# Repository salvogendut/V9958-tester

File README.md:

# V9938 / V9958 Pico Functional Tester

This is an all-through-hole carrier board that performs a behavioral test of a socketed Yamaha V9938 or V9958 video display processor. An original RP2040 Raspberry Pi Pico controls the VDP, tests its dedicated 128 KiB VRAM, measures its clocks and analog RGB outputs, and reports the result on green/red LEDs, USB serial, and an on-screen message through an Omega-compatible DIN RGB output.

The current full-size board is **revision 0.5**. U10 is a through-hole TI LM393P dual comparator and U11 is an SN74HC14N sync buffer. The board passes KiCad ERC, DRC and schematic/PCB parity checks. Qualification on real VDPs is pending. [0.5 Gerbers](fabrication/V9958-Tester-rev0.5-gerbers.zip) · [0.5 BOM](docs/BOM.csv)

For a board already marked **0.4**, fit the MAX942CPA+ specified for that circuit. The LM393P requires the revised input dividers and output circuitry. [0.4 BOM](https://github.com/salvogendut/V9958-tester/blob/81ad3057a48962fd7bea91b546fce25a6f905914/docs/BOM.csv) · [Original 0.3 BOM](docs/V9958-Tester-rev0.3-BOM.csv)

**Disconnect USB and set SW2 to the model printed on the chip before inserting it in U3.** The V9938 uses pin 21 as a video output. Selecting V9958 connects that pin directly to the filtered 5 V rail and can damage a V9938. The original 0.3, B0 and B2 tester PCBs have this direct connection permanently. Use a board marked **0.4 or 0.5**, **B1 or B1.1**, or **B2.1 or B2.2 SRAM** for V9938 testing.

**Polarity correction for full-size v0.3 and early v0.4 boards.** Four electrolytics (C25, C26, C27 and C28) have an extra printed `+` on the negative side. On all seven radial capacitors, fit the positive lead to the rounded-square pad 1 and the striped negative lead to circular pad 2. With the components facing you and the DIN socket at the upper right, the stripe goes on the **right**. The corrected [v0.4 Gerbers](fabrication/V9958-Tester-rev0.4-silk2-gerbers.zip) have a single `+` beside each positive capacitor pad. [Assembly checks](docs/TEST-PROCEDURE.md)

## Board renderings

Select a view to open the full-resolution KiCad rendering.

| PCB revision | Assembled | Bare component side | Bare solder side |
|---|---|---|---|
| **Full-size tester 0.5** · [Assembled top view](docs/V9958-Tester-top.png) |  |  |  |
| **Compact DRAM tester B1.1** · [Assembled top view](revision-b/docs/V9958-Tester-RevB-top.png) |  |  |  |
| **Compact SRAM tester B2.2** · [Assembled top view](revision-b2-sram/docs/V9958-Tester-RevB2-SRAM-top.png) |  |  |  |

On the full-size 0.5, the RGB cable plugs into J1 from outside the top edge. The four VRAM sockets sit above U3, and the Pico USB connector faces right. SW2 sits above the TEST button. Disconnect USB before selecting the VDP model. All four boards print component references and BOM values on the component side, including the 1% resistor tolerances.

[Earlier renderings for 0.4, B1 and B2.1](https://github.com/salvogendut/V9958-tester/blob/81ad3057a48962fd7bea91b546fce25a6f905914/README.md#board-renderings)

## Revision B family and video daughterboard

Revision B separates the functional tester from the optional monitor output. The
[Revision B core](revision-b/) keeps the socketed VDP, four 41464 VRAMs, one
SN74LVC245 data transceiver, one SN74LVC244 monitor buffer, the oscillator,
power integrity, RGB loads and Pico. The Pico drives the VDP control inputs
directly through 330-ohm series resistors. The CXA1645 and DIN connector have
moved to a separate [RGB DIN daughterboard](video-daughterboard/).

The experimental [Revision B2 SRAM board](revision-b2-sram/) replaces the four
41464 DRAMs with one AS6C1008-55PCN 128Kx8 SRAM, an SN74AHCT573 row-address
latch and an SN74AHCT08 CAS-to-output-enable gate. The Pico still controls and
tests the selected VDP; it does not emulate the timing-critical video RAM bus.

B2 is smaller at 160 x 110 mm and remains entirely through-hole. It includes
dedicated `/RAS`, `/CAS0`, `/CAS1`, SRAM `/OE` and SRAM `/WE` test points. Its
static KiCad checks pass, but its narrow SRAM timing margin has not been
qualified on hardware. Do not use an unqualified B2 fixture to reject a VDP;
confirm failures on a qualified DRAM fixture or a working Omega configured for that chip.

The two boards use a keyed, straight-through 2x3 IDC cable: pin 1 GND, pin 2
+5 V, pin 3 red, pin 4 green, pin 5 blue and pin 6 composite sync. Revision B
passes or fails without the daughterboard; connect it only when an Omega-style
15.6 kHz RGB monitor output and on-screen result are wanted. Both designs are
unbuilt prototypes and have their own BOM, schematic PDF, validation record,
assembly drawing and Gerber archive.

## What it tests

- CPU bus operation through 3.3 V/5 V level translation.
- VDP identification through status register 1, bits 5–1. ID 0 selects V9938 tests and ID 2 selects V9958 tests. Other IDs fail identification.
- Two full address-dependent passes over 128 KiB of local VRAM.
- Approximately 3.58 MHz CPUCLK and 15.6 kHz HSYNC/CSYNC.
- Vertical-blank interrupt assertion and status acknowledgement.
- Red, green, and blue analog-channel response through loaded, divided ADC inputs.

A green LED means all behavioral checks passed. A red LED means at least one check failed; USB serial gives the stage and measurements. A pass is **not forensic proof** that the package was manufactured by Yamaha. A sufficiently compatible clone could pass.

The firmware also leaves a 40-column PAL result screen visible on the DIN RGB output. It shows `PASS` or `FAIL`, the numeric stage code, and the failed subsystem. The screen and USB result identify the detected model. Compare it with the package marking.

## Construction

The tester PCB itself uses no SMD parts. Fit the Pico on two 1x20 through-hole socket strips; the Pico module is, of course, an already assembled module containing SMD components. Use sockets for U1–U9, including a suitable SDIP-64 socket at U3. On revision 0.5, fit the LM393P at U10, the SN74HC14N at U11, and the C&K JS202011CQN model selector at SW2.

Important parts:

- U3 footprint: custom SDIP-64, 1.778 mm pin pitch, 19.05 mm row spacing.
- U5–U8: four 41464-compatible 64Kx4 DRAMs, 120 ns or faster.
- U1: SN74LVC245AN, powered from 3.3 V.
- U2: SN74AHCT244N, powered from 5 V.
- U4: SN74LVC244AN, powered from 3.3 V.
- U9: CXA1645P in DIP-24, used as the three-channel 75-ohm RGB cable buffer.
- J1 takes a Same Sky **SDS-80J**, a standard full-size 270° right-angle DIN-8 socket. It accepts an Omega-wired RGB cable. The shielded SDF-80J with a date code after 03/03/2022 also fits the PCB drawing. [SDS-80J drawing, p. 5](https://www.sameskydevices.com/product/resource/sds-j.pdf) · [DigiKey Italy](https://www.digikey.it/it/products/detail/same-sky-formerly-cui-devices/SDS-80J/97041)
- Y1: 21.477270 MHz crystal; C1 is the 30 pF oscillator trimmer.
- F1: Bourns MF-RHT100 resettable fuse, 1.0 A hold / 1.8 A trip.

The grouped [BOM](docs/BOM.csv), [schematic PDF](docs/V9958-Tester-Schematic.pdf), and [test procedure](docs/TEST-PROCEDURE.md) are in `docs/`. The [fabrication directory](fabrication/) contains the Gerbers and drill files for each full-size dual-model revision.

## Power and handling

Power the board only through the Pico USB connector, from a good 5 V supply capable of at least 1 A. For first power-up, use a current-limited bench supply or USB power limiter. Never insert or remove the V9958, VRAM, logic chips, or Pico while powered.

The board provides native 15.6 kHz PAL RGB through J1. It is suitable for an Omega/MSX RGB cable and a compatible RGB monitor or SCART input; it is **not 31 kHz VGA** and must not be connected to a VGA-only display. J1 follows the Omega assignments: pin 1 ground, pin 3 AV control, pin 4 attenuated composite sync, pin 5 RGB/YS control, pin 6 red, pin 7 green, and pin 8 blue. Pin 2 (audio on an Omega) is unconnected because the tester has no audio source.

U9 reproduces the Omega-style buffered RGB path: 0.1 uF input coupling, CXA1645 clamping/drivers, and 75 ohm plus 220 uF output coupling per colour. J1 pin 4 carries sync only, not composite video. Scope points remain available for 5 V, 3.3 V, ground, CPUCLK, HSYNC, CSYNC, and raw R/G/B.

## Firmware

Firmware source is in `firmware/`. With a Pico SDK toolchain installed:

```sh
export PICO_SDK_PATH=/path/to/pico-sdk
cmake -S firmware -B firmware/build -DPICO_BOARD=pico
cmake --build firmware/build -j4
```

Copy the supplied [full-size tester UF2](firmware/v9958_tester.uf2) or your local build to a Pico in BOOTSEL mode. The program runs once at power-up and again whenever SW1 is pressed. USB CDC serial prints the clock counts, VDP ID, first VRAM mismatch if any, interrupt result, RGB ADC readings, and final stage code. At completion it programs the VDP for PAL text mode and shows the same result through J1.

The compact boards use the shared source. Their images are [B1/B1.1 DRAM](revision-b/firmware/v9958_tester_revb.uf2) and [B2.1/B2.2 SRAM](revision-b2-sram/firmware/v9958_tester_revb2.uf2). They have no TEST
button; send `R` over USB serial to repeat the test.

## Design files and regeneration

- `V9958-Tester.kicad_sch`: native KiCad 10 schematic.
- `V9958-Tester.kicad_pcb`: two-layer routed board with GND pours.
- `V9958-Tester.kicad_pro`: project settings.
- `V9958-Tester.pretty/` contains the VDP socket, trimmer, and Same Sky DIN-8 footprints.
- `tools/`: deterministic schematic, footprint, placement, finish, and BOM generators.

The routing was completed with Freerouting and then imported and checked by KiCad. The checked-in PCB is the release artifact; rerunning the placement generator intentionally produces an unrouted board.

## Known prototype limitations

- RGB pass thresholds are conservative defaults and must be calibrated on known-good samples of both models.
- The full VRAM test and VDP port timing must be verified on physical hardware.
- Socket/ZIF mechanical fit must be checked against the exact part you intend to buy.
- CXA1645 RGB amplitude, sync attenuation, DIN socket fit, and compatibility with the intended Omega RGB cable must be confirmed on the first prototype.
- The test identifies behavior, not die markings or provenance.

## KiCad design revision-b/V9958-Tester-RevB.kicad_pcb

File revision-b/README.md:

# V9958 Tester Revision B

**Use PCB B1 or B1.1 for V9938 or V9958.** Disconnect USB, set SW2 to the package marking, then insert the DUT. Earlier boards without SW2 connect pin 21 directly to 5 V and can damage a V9938. See the [selector checks](docs/TEST-PROCEDURE.md).

PCB **B1.1** uses an LM393P at U10 and an SN74HC14N at U11. PCB **B1** uses a MAX942CPA+ at U10. [B1.1 BOM](docs/BOM.csv) · [B1.1 Gerbers](fabrication/V9958-Tester-RevB-B1.1-gerbers.zip) · [B1 BOM](https://github.com/salvogendut/V9958-tester/blob/81ad3057a48962fd7bea91b546fce25a6f905914/revision-b/docs/BOM.csv)

Revision B is the minimal all-through-hole V9938/V9958 functional tester. It is a
170 x 118 mm, two-layer core board powered through the Pico USB connector. It
performs the same VDP identification, CPU bus, 128 KiB VRAM, sync, interrupt
and RGB-response tests as the full-size tester without requiring a CXA1645 or monitor.

## B1.1 board renderings

| Assembled angled view | Assembled top view |
|---|---|
|  |  |

| Bare component side | Bare solder side |
|---|---|
|  |  |

## What was simplified

- The SN74AHCT244 control buffer is gone. Pico 3.3 V outputs satisfy the
  V9958's 2.2 V minimum high threshold and reach it through 330-ohm resistors.
- The CXA1645 and DIN connector are on the optional video daughterboard.
- The TEST button is omitted. Send `R` over USB serial to repeat a run.
- The V9958, four 41464 VRAMs, crystal network, RGB loads, decoupling and
  filtered 5 V rail remain because they are intrinsic to a trustworthy test.
- U4 remains an SN74LVC244 powered at 3.3 V. Its 5 V-tolerant inputs avoid
  loading the VDP clock output. U10 and U11 condition HSYNC and CSYNC before U4.

J1 is a keyed 2x3 IDC video expansion header: 1 GND, 2 +5 V, 3 red, 4 green,
5 blue and 6 CSYNC. Use a straight-through cable to the matching daughterboard.

The grouped [BOM](docs/BOM.csv), [schematic PDF](docs/V9958-Tester-RevB-Schematic.pdf),
[test procedure](docs/TEST-PROCEDURE.md), [design notes](docs/DESIGN-NOTES.md)
and [validation record](docs/VALIDATION.md) are included. This is an unbuilt,
unvalidated prototype; zero ERC/DRC violations do not substitute for physical
qualification with known-good and known-bad samples of both models.

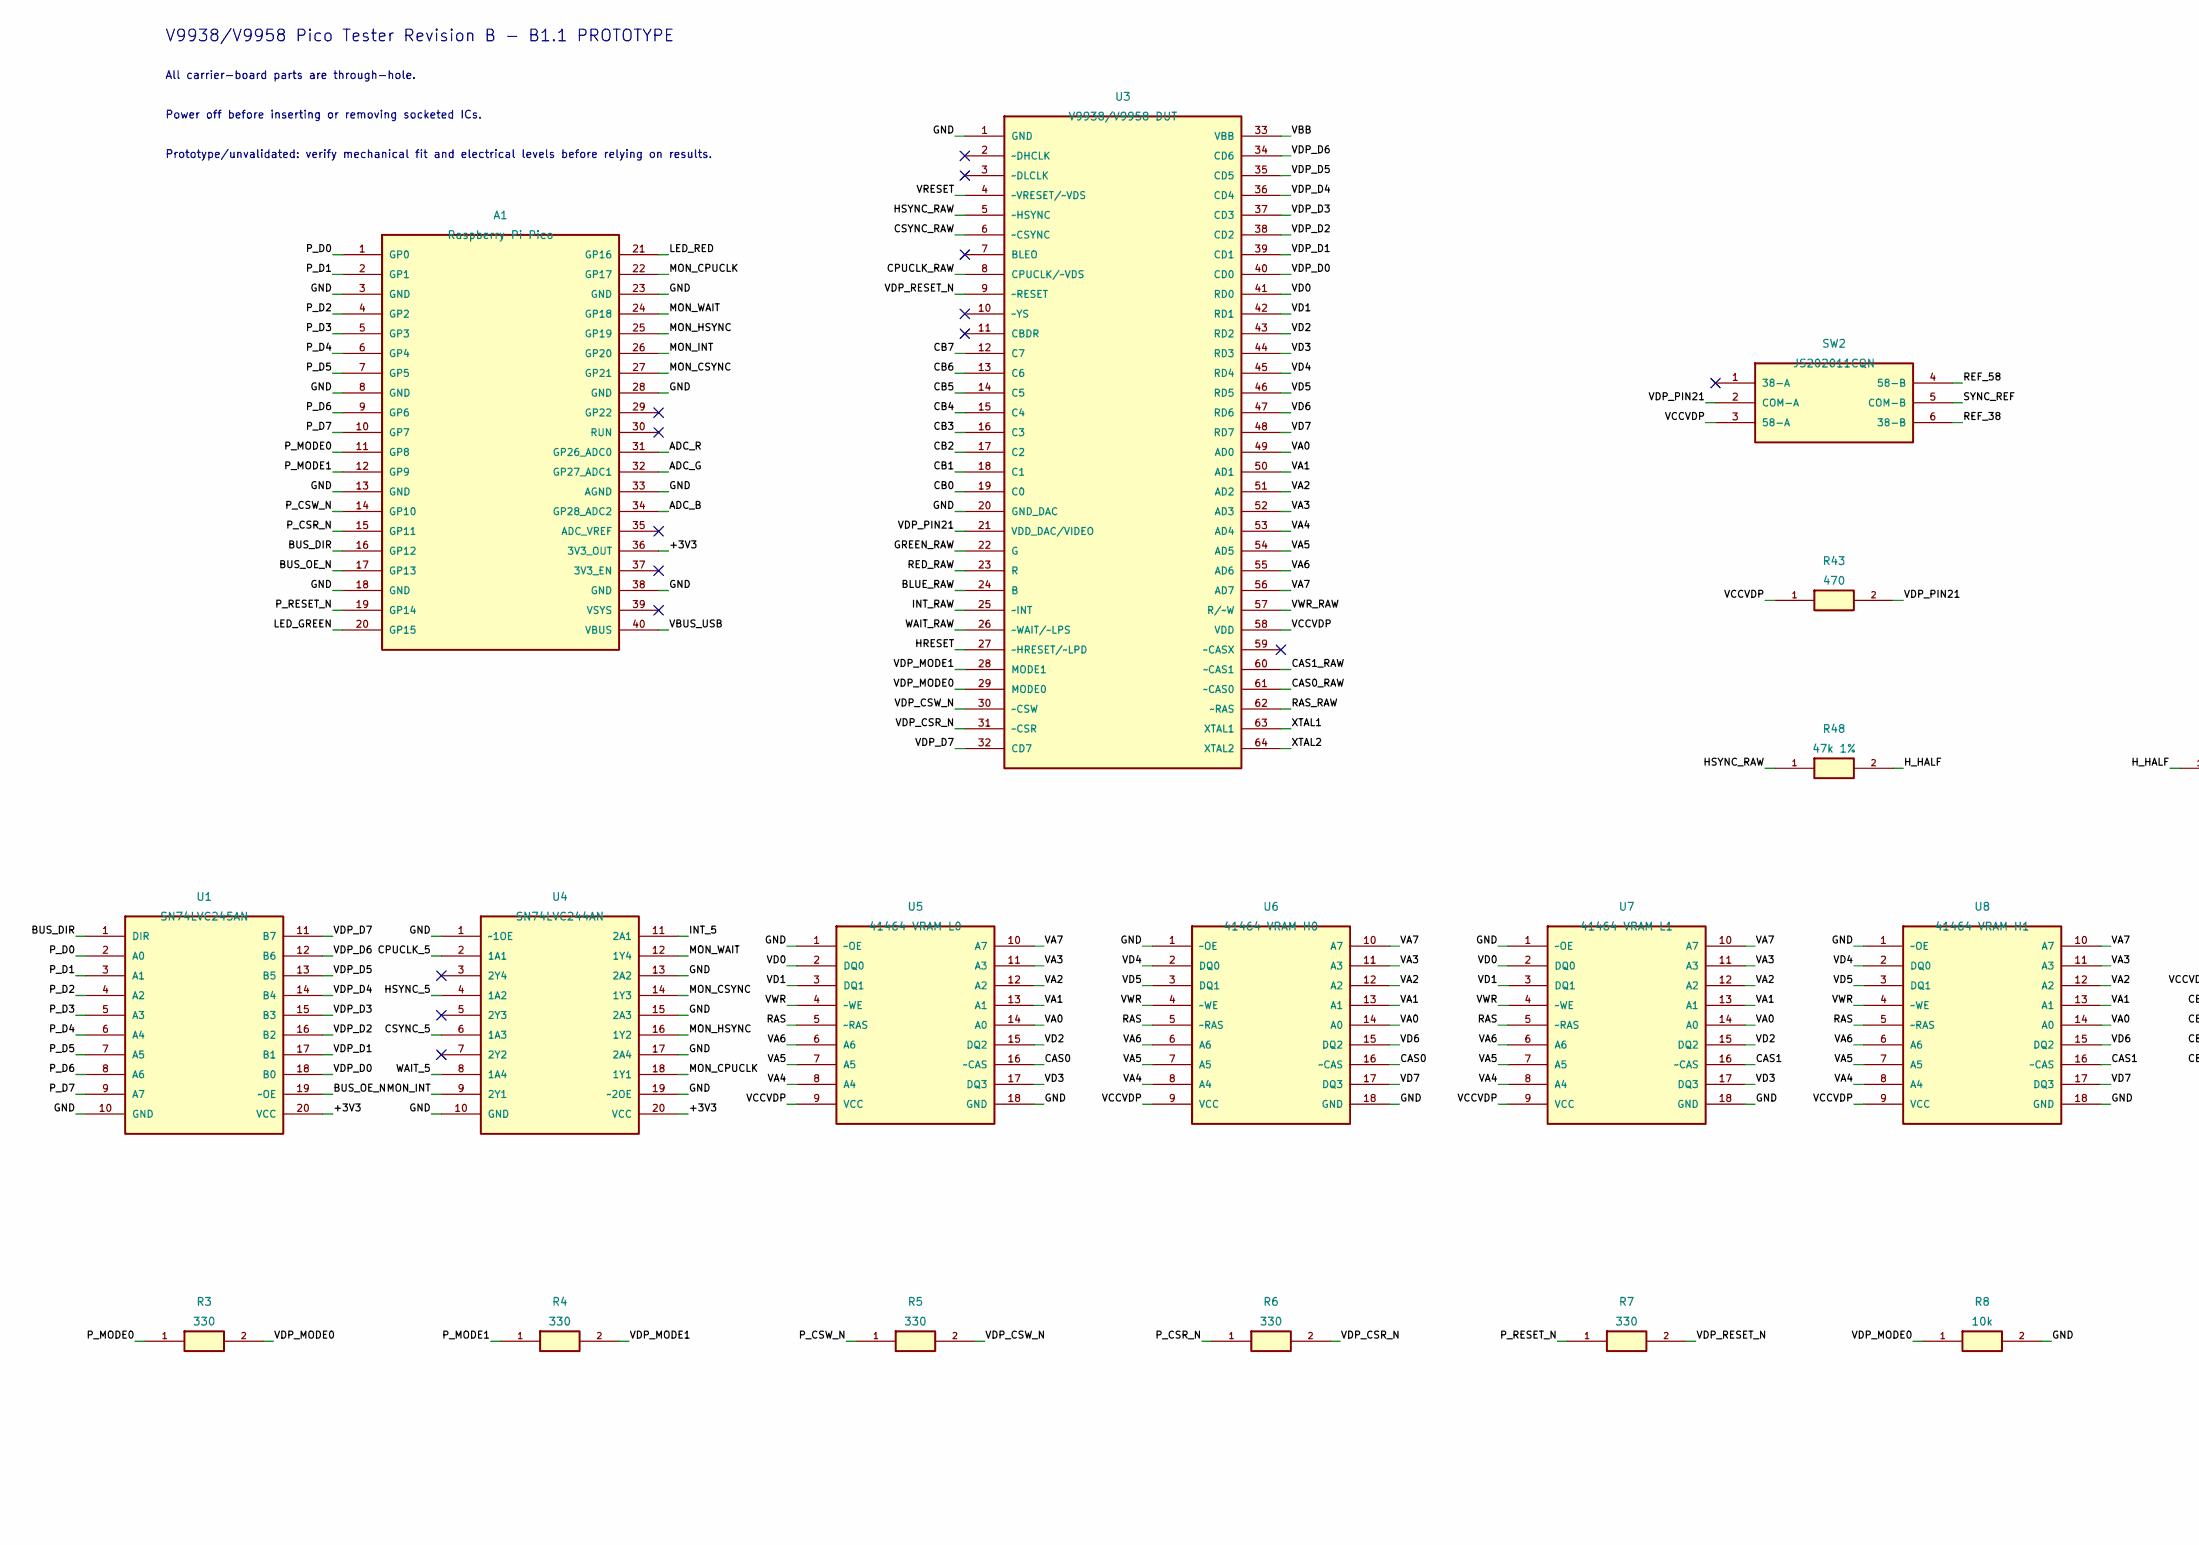
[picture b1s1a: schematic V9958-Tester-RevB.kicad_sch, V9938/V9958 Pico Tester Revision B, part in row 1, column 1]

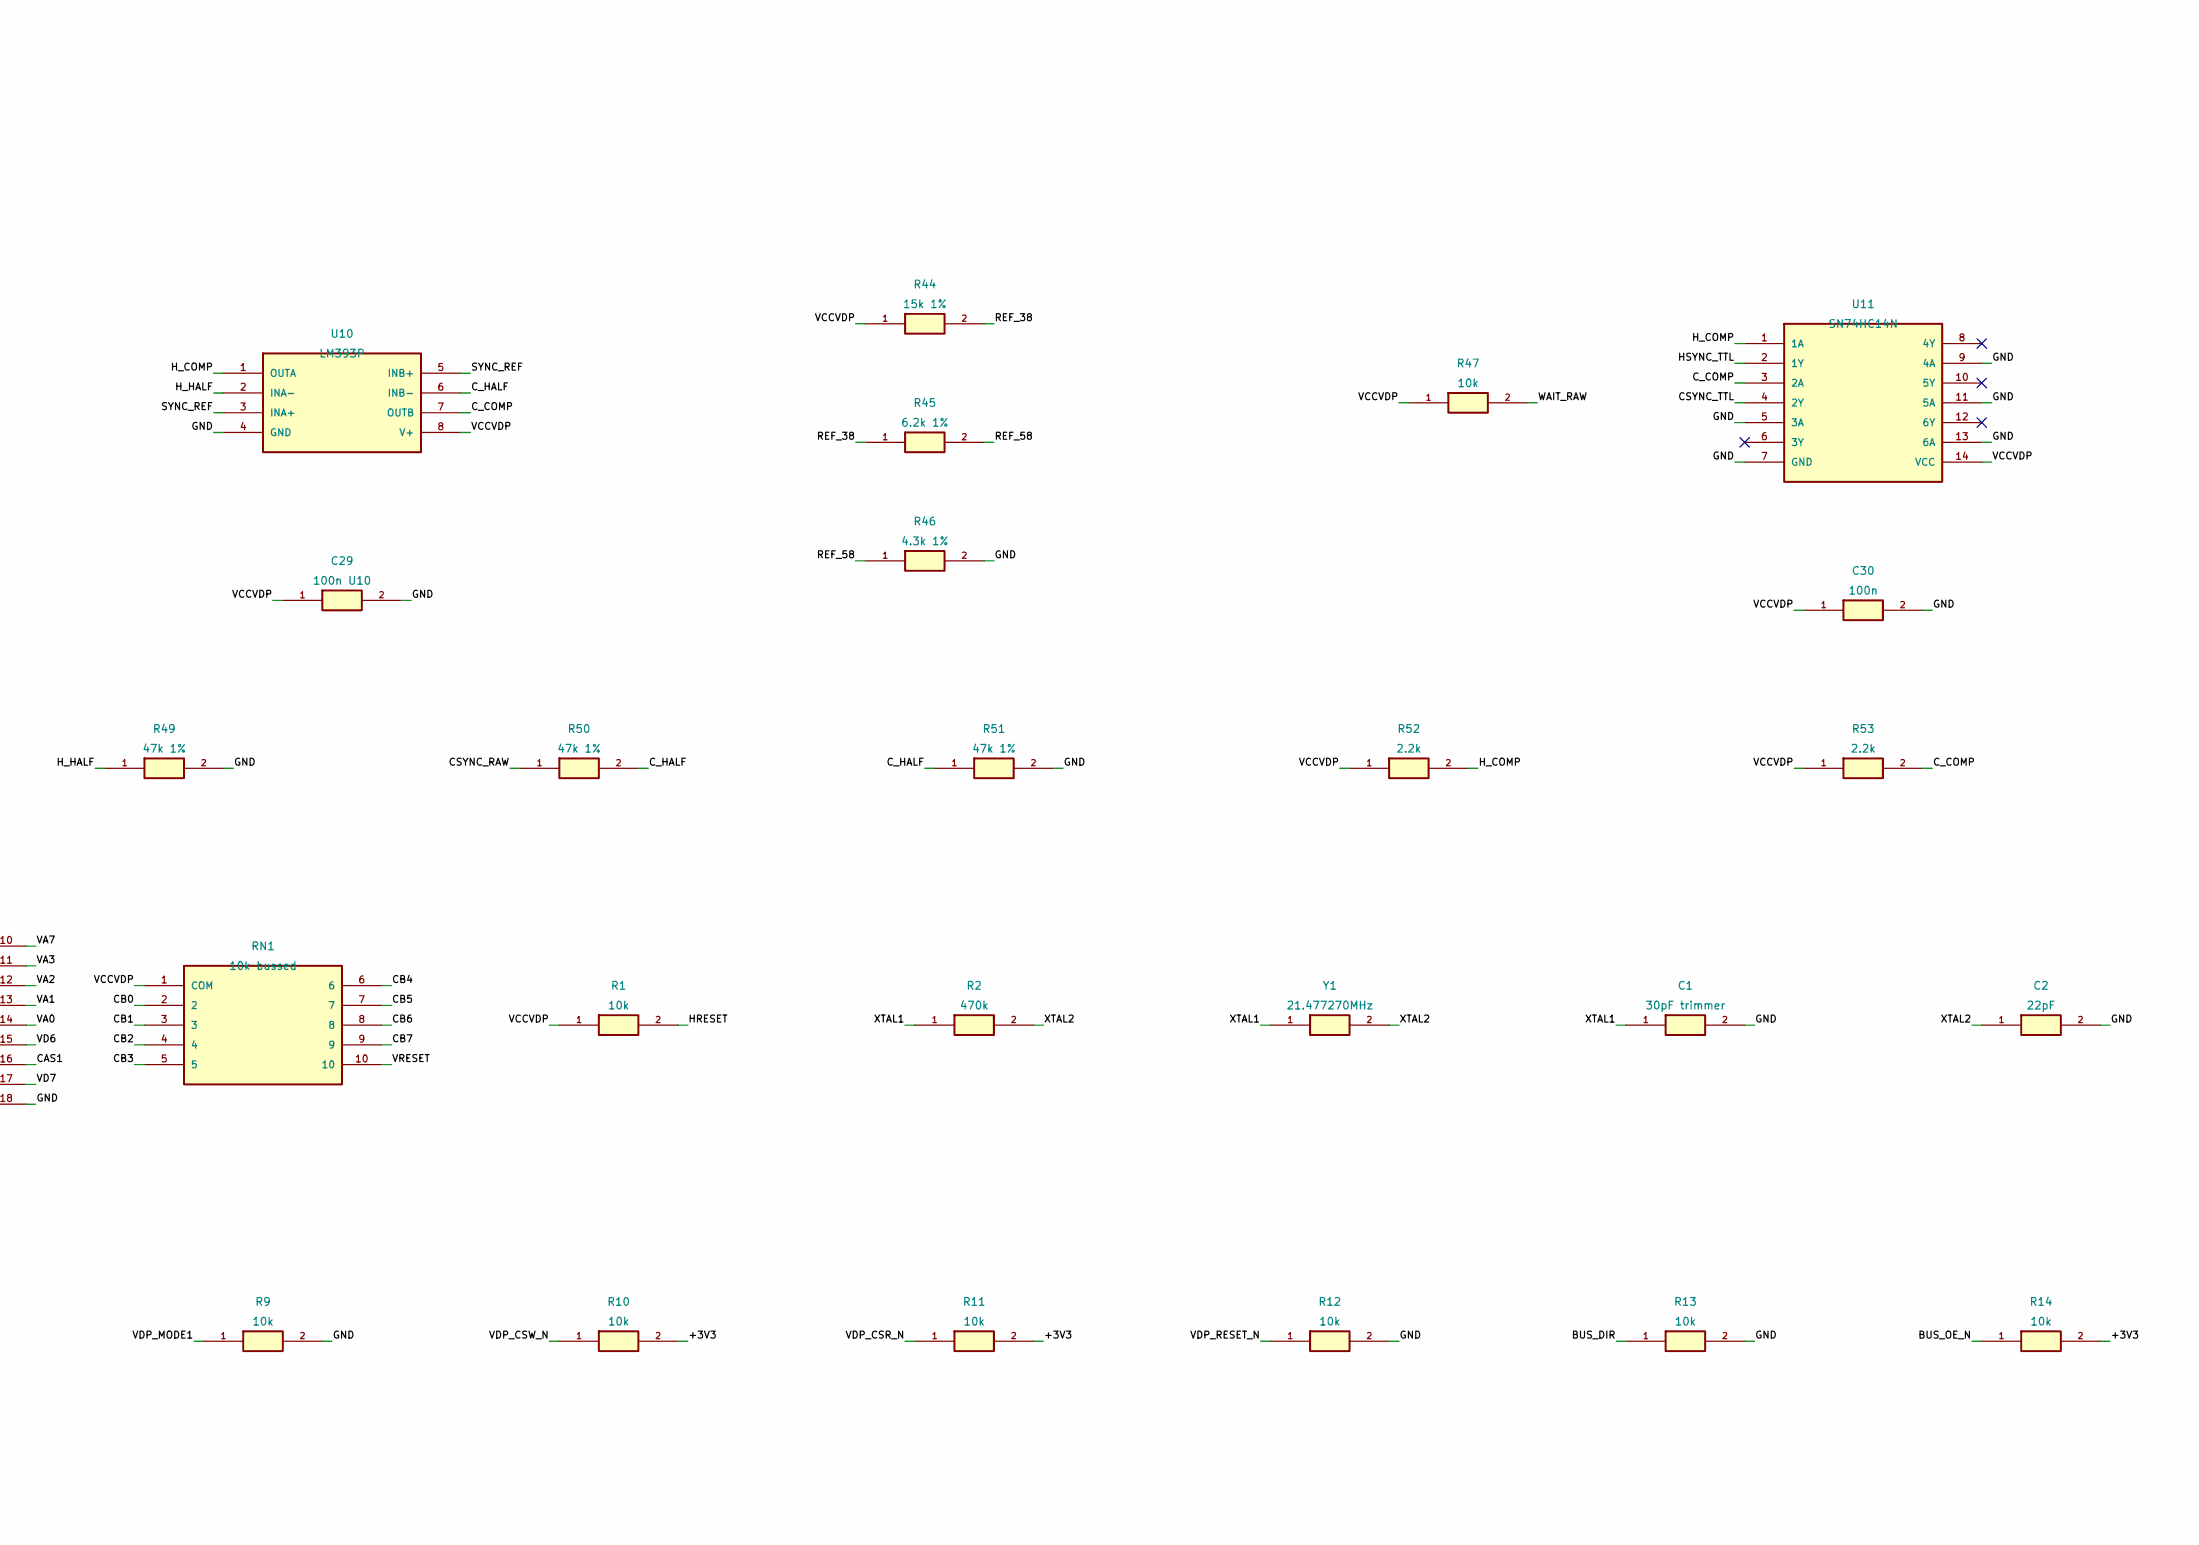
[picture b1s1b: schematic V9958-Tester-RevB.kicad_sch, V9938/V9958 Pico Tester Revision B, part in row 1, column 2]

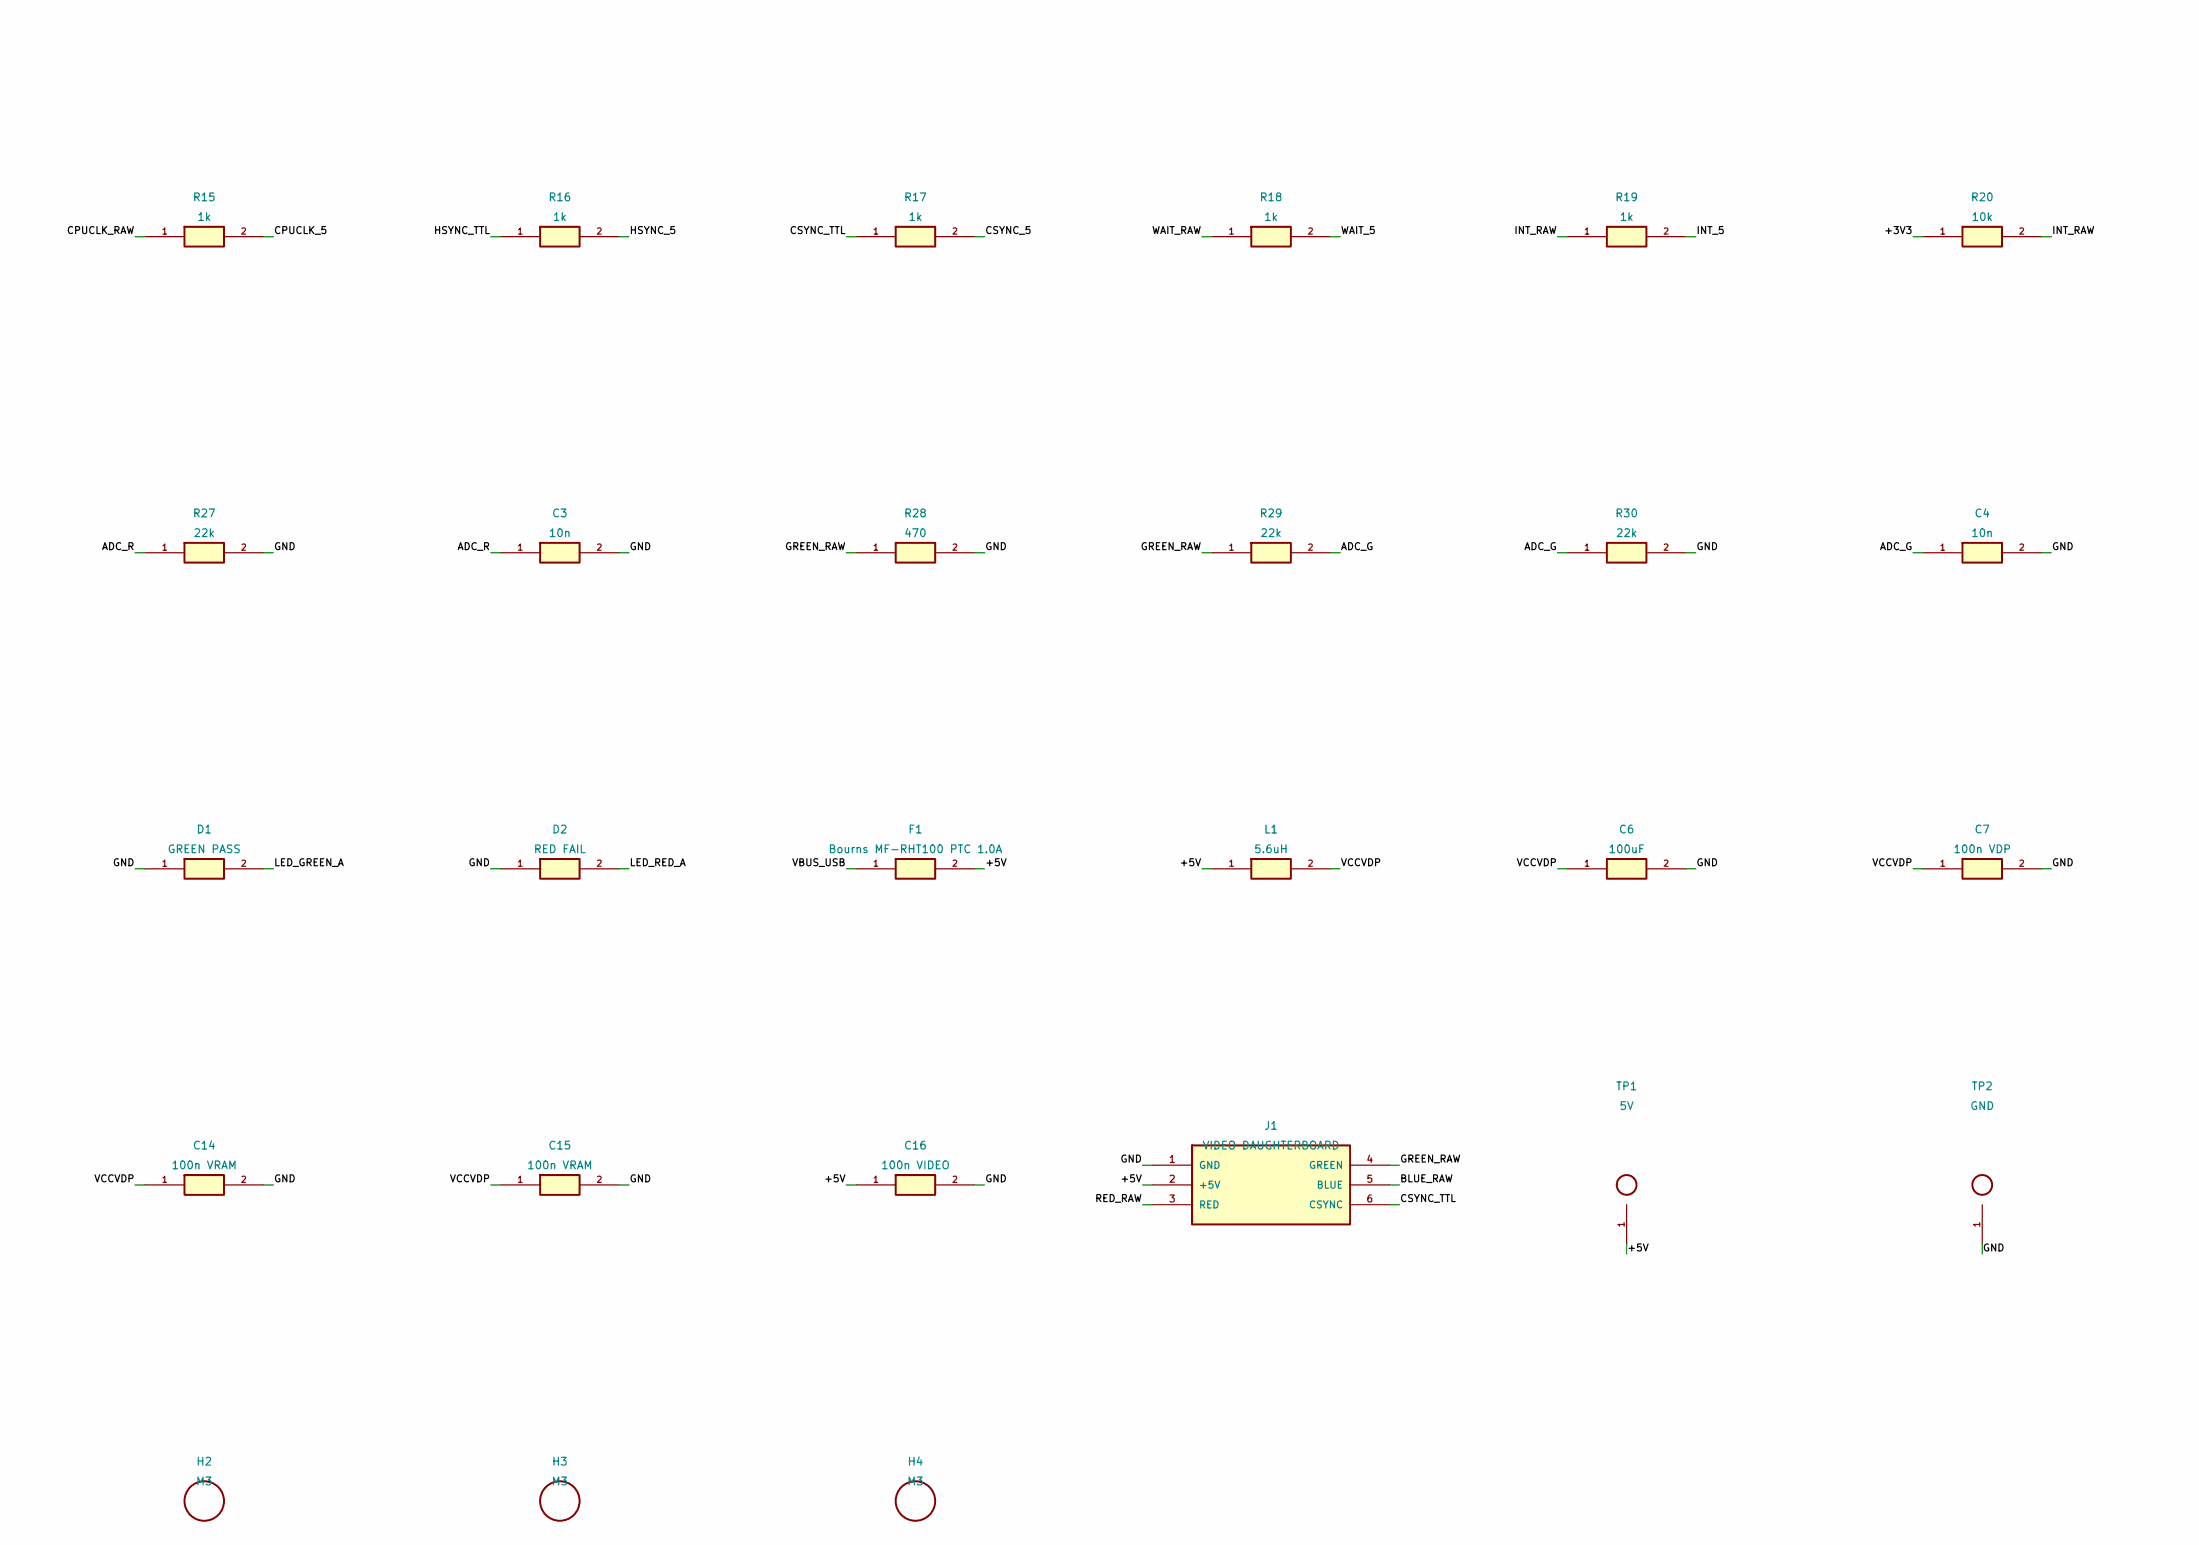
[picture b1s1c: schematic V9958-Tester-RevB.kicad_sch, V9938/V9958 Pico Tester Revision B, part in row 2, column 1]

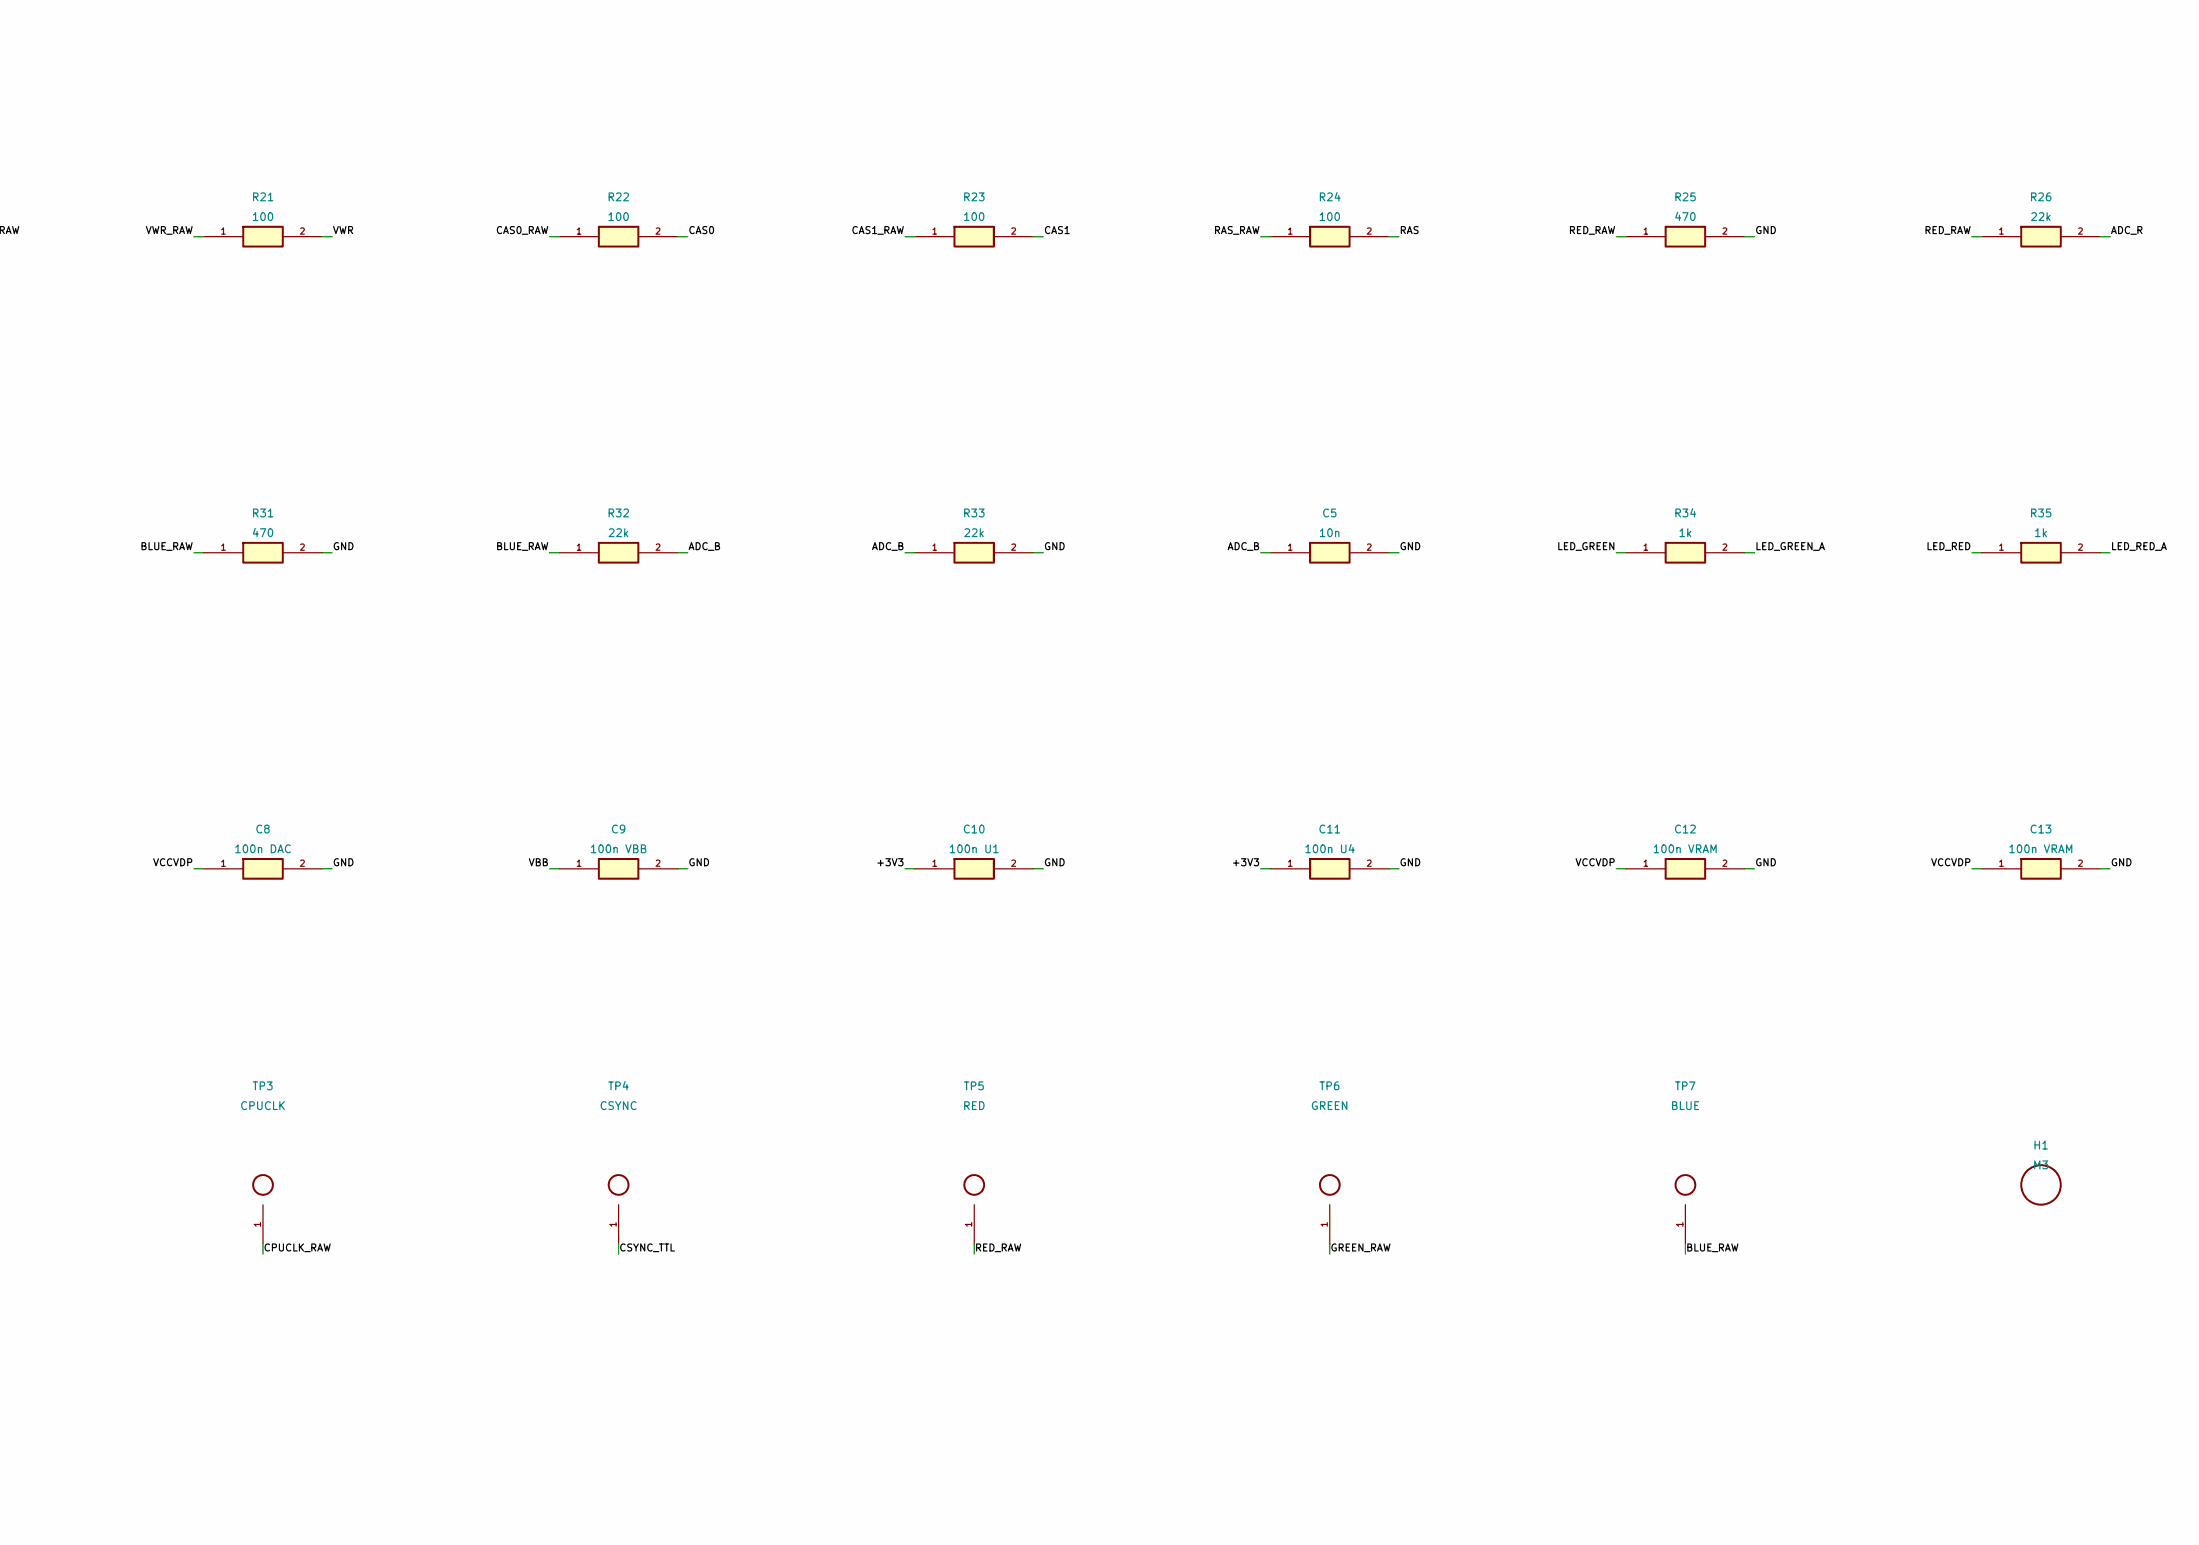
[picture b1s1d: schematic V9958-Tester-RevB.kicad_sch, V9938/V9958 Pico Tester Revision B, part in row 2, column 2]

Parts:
A1: Raspberry Pi Pico; RaspberryPi_Pico_Common_THT
C1: 30pF trimmer; C_Trim_P5.00mm
C2: 22pF; C_Disc_D5.0mm_W2.5mm_P5.00mm
C3, C4, C5: 10n; C_Disc_D5.0mm_W2.5mm_P5.00mm
C6: 100uF; CP_Radial_D5.0mm_P2.00mm
C7: 100n VDP; C_Disc_D5.0mm_W2.5mm_P5.00mm
C8: 100n DAC; C_Disc_D5.0mm_W2.5mm_P5.00mm
C9: 100n VBB; C_Disc_D5.0mm_W2.5mm_P5.00mm
C10: 100n U1; C_Disc_D5.0mm_W2.5mm_P5.00mm
C11: 100n U4; C_Disc_D5.0mm_W2.5mm_P5.00mm
C12, C13, C14, C15: 100n VRAM; C_Disc_D5.0mm_W2.5mm_P5.00mm
C16: 100n VIDEO; C_Disc_D5.0mm_W2.5mm_P5.00mm
C29: 100n U10; C_Disc_D5.0mm_W2.5mm_P5.00mm
C30: 100n; C_Disc_D5.0mm_W2.5mm_P5.00mm
D1: GREEN PASS; LED_D5.0mm
D2: RED FAIL; LED_D5.0mm
F1: Bourns MF-RHT100 PTC 1.0A; Fuse_Bourns_MF-RHT100
H1, H2, H3, H4: M3; MountingHole_3.2mm_M3
J1: VIDEO DAUGHTERBOARD; IDC-Header_2x03_P2.54mm_Vertical
L1: 5.6uH; L_Axial_L14.0mm_D4.5mm_P15.24mm_Horizontal_Fastron_LACC
R1, R8, R9, R10, R11, R12, R13, R14, R20, R47: 10k; R_Axial_DIN0207_L6.3mm_D2.5mm_P7.62mm_Horizontal
R2: 470k; R_Axial_DIN0207_L6.3mm_D2.5mm_P7.62mm_Horizontal
R3, R4, R5, R6, R7: 330; R_Axial_DIN0207_L6.3mm_D2.5mm_P7.62mm_Horizontal
R15, R16, R17, R18, R19, R34, R35: 1k; R_Axial_DIN0207_L6.3mm_D2.5mm_P7.62mm_Horizontal
R21, R22, R23, R24: 100; R_Axial_DIN0207_L6.3mm_D2.5mm_P7.62mm_Horizontal
R25, R28, R31, R43: 470; R_Axial_DIN0207_L6.3mm_D2.5mm_P7.62mm_Horizontal
R26, R27, R29, R30, R32, R33: 22k; R_Axial_DIN0207_L6.3mm_D2.5mm_P7.62mm_Horizontal
R44: 15k 1%; R_Axial_DIN0207_L6.3mm_D2.5mm_P7.62mm_Horizontal
R45: 6.2k 1%; R_Axial_DIN0207_L6.3mm_D2.5mm_P7.62mm_Horizontal
R46: 4.3k 1%; R_Axial_DIN0207_L6.3mm_D2.5mm_P7.62mm_Horizontal
R48, R49, R50, R51: 47k 1%; R_Axial_DIN0207_L6.3mm_D2.5mm_P7.62mm_Horizontal
R52, R53: 2.2k; R_Axial_DIN0207_L6.3mm_D2.5mm_P7.62mm_Horizontal
RN1: 10k bussed; R_Array_SIP10
SW2: JS202011CQN; SW_CK_JS202011CQN_DPDT_Straight
TP1: 5V; TestPoint_THTPad_D2.0mm_Drill1.0mm
TP2: GND; TestPoint_THTPad_D2.0mm_Drill1.0mm
TP3: CPUCLK; TestPoint_THTPad_D2.0mm_Drill1.0mm
TP4: CSYNC; TestPoint_THTPad_D2.0mm_Drill1.0mm
TP5: RED; TestPoint_THTPad_D2.0mm_Drill1.0mm
TP6: GREEN; TestPoint_THTPad_D2.0mm_Drill1.0mm
TP7: BLUE; TestPoint_THTPad_D2.0mm_Drill1.0mm
U1: SN74LVC245AN; DIP-20_W7.62mm_Socket_LongPads
U3: V9938/V9958 DUT; SDIP-64_W19.05mm_P1.778mm_Socket
U4: SN74LVC244AN; DIP-20_W7.62mm_Socket_LongPads
U5: 41464 VRAM L0; DIP-18_W7.62mm_Socket_LongPads
U6: 41464 VRAM H0; DIP-18_W7.62mm_Socket_LongPads
U7: 41464 VRAM L1; DIP-18_W7.62mm_Socket_LongPads
U8: 41464 VRAM H1; DIP-18_W7.62mm_Socket_LongPads
U10: LM393P; DIP-8_W7.62mm
U11: SN74HC14N; DIP-14_W7.62mm
Y1: 21.477270MHz; Crystal_HC49-U_Vertical

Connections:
/+3V3: A1.36 (3V3_OUT), C10.1, C11.1, R10.2, R11.2, R14.2, R20.1, U1.20 (VCC), U4.20 (VCC)
/+5V: C16.1, F1.2, J1.2 (+5V), L1.1, TP1.1
/ADC_B: A1.34 (GP28_ADC2), C5.1, R32.2, R33.1
/ADC_G: A1.32 (GP27_ADC1), C4.1, R29.2, R30.1
/ADC_R: A1.31 (GP26_ADC0), C3.1, R26.2, R27.1
/BLUE_RAW: J1.5 (BLUE), R31.1, R32.1, TP7.1, U3.24 (B)
/BUS_DIR: A1.16 (GP12), R13.1, U1.1 (DIR)
/BUS_OE_N: A1.17 (GP13), R14.1, U1.19 (~OE)
/CAS0: R22.2, U5.16 (~CAS), U6.16 (~CAS)
/CAS0_RAW: R22.1, U3.61 (~CAS0)
/CAS1: R23.2, U7.16 (~CAS), U8.16 (~CAS)
/CAS1_RAW: R23.1, U3.60 (~CAS1)
/CB0: RN1.2, U3.19 (C0)
/CB1: RN1.3, U3.18 (C1)
/CB2: RN1.4, U3.17 (C2)
/CB3: RN1.5, U3.16 (C3)
/CB4: RN1.6, U3.15 (C4)
/CB5: RN1.7, U3.14 (C5)
/CB6: RN1.8, U3.13 (C6)
/CB7: RN1.9, U3.12 (C7)
/CPUCLK_5: R15.2, U4.2 (1A1)
/CPUCLK_RAW: R15.1, TP3.1, U3.8 (CPUCLK/~VDS)
/CSYNC_5: R17.2, U4.6 (1A3)
/CSYNC_RAW: R50.1, U3.6 (~CSYNC)
/CSYNC_TTL: J1.6 (CSYNC), R17.1, TP4.1, U11.4 (2Y)
/C_COMP: R53.2, U10.7 (OUTB), U11.3 (2A)
/C_HALF: R50.2, R51.1, U10.6 (INB-)
/GND: A1.3 (GND), A1.8 (GND), A1.13 (GND), A1.18 (GND), A1.23 (GND), A1.28 (GND), A1.33 (AGND), A1.38 (GND), C1.2, C2.2, C3.2, C4.2, C5.2, C6.2, C7.2, C8.2, C9.2, C10.2, C11.2, C12.2, C13.2, C14.2, C15.2, C16.2, C29.2, C30.2, D1.1, D2.1, J1.1 (GND), R8.2, R9.2, R12.2, R13.2, R25.2, R27.2, R28.2, R30.2, R31.2, R33.2, R46.2, R49.2, R51.2, TP2.1, U1.10 (GND), U3.1 (GND), U3.20 (GND_DAC), U4.1 (~1OE), U4.10 (GND), U4.13 (2A2), U4.15 (2A3), U4.17 (2A4), U4.19 (~2OE), U5.1 (~OE), U5.18 (GND), U6.1 (~OE), U6.18 (GND), U7.1 (~OE), U7.18 (GND), U8.1 (~OE), U8.18 (GND), U10.4 (GND), U11.5 (3A), U11.7 (GND), U11.9 (4A), U11.11 (5A), U11.13 (6A)
/GREEN_RAW: J1.4 (GREEN), R28.1, R29.1, TP6.1, U3.22 (G)
/HRESET: R1.2, U3.27 (~HRESET/~LPD)
/HSYNC_5: R16.2, U4.4 (1A2)
/HSYNC_RAW: R48.1, U3.5 (~HSYNC)
/HSYNC_TTL: R16.1, U11.2 (1Y)
/H_COMP: R52.2, U10.1 (OUTA), U11.1 (1A)
/H_HALF: R48.2, R49.1, U10.2 (INA-)
/INT_5: R19.2, U4.11 (2A1)
/INT_RAW: R19.1, R20.2, U3.25 (~INT)
/LED_GREEN: A1.20 (GP15), R34.1
/LED_GREEN_A: D1.2, R34.2
/LED_RED: A1.21 (GP16), R35.1
/LED_RED_A: D2.2, R35.2
/MON_CPUCLK: A1.22 (GP17), U4.18 (1Y1)
/MON_CSYNC: A1.27 (GP21), U4.14 (1Y3)
/MON_HSYNC: A1.25 (GP19), U4.16 (1Y2)
/MON_INT: A1.26 (GP20), U4.9 (2Y1)
/MON_WAIT: A1.24 (GP18), U4.12 (1Y4)
/P_CSR_N: A1.15 (GP11), R6.1
/P_CSW_N: A1.14 (GP10), R5.1
/P_D0: A1.1 (GP0), U1.2 (A0)
/P_D1: A1.2 (GP1), U1.3 (A1)
/P_D2: A1.4 (GP2), U1.4 (A2)
/P_D3: A1.5 (GP3), U1.5 (A3)
/P_D4: A1.6 (GP4), U1.6 (A4)
/P_D5: A1.7 (GP5), U1.7 (A5)
/P_D6: A1.9 (GP6), U1.8 (A6)
/P_D7: A1.10 (GP7), U1.9 (A7)
/P_MODE0: A1.11 (GP8), R3.1
/P_MODE1: A1.12 (GP9), R4.1
/P_RESET_N: A1.19 (GP14), R7.1
/RAS: R24.2, U5.5 (~RAS), U6.5 (~RAS), U7.5 (~RAS), U8.5 (~RAS)
/RAS_RAW: R24.1, U3.62 (~RAS)
/RED_RAW: J1.3 (RED), R25.1, R26.1, TP5.1, U3.23 (R)
/REF_38: R44.2, R45.1, SW2.6 (38-B)
/REF_58: R45.2, R46.1, SW2.4 (58-B)
/SYNC_REF: SW2.5 (COM-B), U10.3 (INA+), U10.5 (INB+)
/VA0: U3.49 (AD0), U5.14 (A0), U6.14 (A0), U7.14 (A0), U8.14 (A0)
/VA1: U3.50 (AD1), U5.13 (A1), U6.13 (A1), U7.13 (A1), U8.13 (A1)
/VA2: U3.51 (AD2), U5.12 (A2), U6.12 (A2), U7.12 (A2), U8.12 (A2)
/VA3: U3.52 (AD3), U5.11 (A3), U6.11 (A3), U7.11 (A3), U8.11 (A3)
/VA4: U3.53 (AD4), U5.8 (A4), U6.8 (A4), U7.8 (A4), U8.8 (A4)
/VA5: U3.54 (AD5), U5.7 (A5), U6.7 (A5), U7.7 (A5), U8.7 (A5)
/VA6: U3.55 (AD6), U5.6 (A6), U6.6 (A6), U7.6 (A6), U8.6 (A6)
/VA7: U3.56 (AD7), U5.10 (A7), U6.10 (A7), U7.10 (A7), U8.10 (A7)
/VBB: C9.1, U3.33 (VBB)
/VBUS_USB: A1.40 (VBUS), F1.1
/VCCVDP: C6.1, C7.1, C8.1, C12.1, C13.1, C14.1, C15.1, C29.1, C30.1, L1.2, R1.1, R43.1, R44.1, R47.1, R52.1, R53.1, RN1.1 (COM), SW2.3 (58-A), U3.58 (VDD), U5.9 (VCC), U6.9 (VCC), U7.9 (VCC), U8.9 (VCC), U10.8 (V+), U11.14 (VCC)
/VD0: U3.41 (RD0), U5.2 (DQ0), U7.2 (DQ0)
/VD1: U3.42 (RD1), U5.3 (DQ1), U7.3 (DQ1)
/VD2: U3.43 (RD2), U5.15 (DQ2), U7.15 (DQ2)
/VD3: U3.44 (RD3), U5.17 (DQ3), U7.17 (DQ3)
/VD4: U3.45 (RD4), U6.2 (DQ0), U8.2 (DQ0)
/VD5: U3.46 (RD5), U6.3 (DQ1), U8.3 (DQ1)
/VD6: U3.47 (RD6), U6.15 (DQ2), U8.15 (DQ2)
/VD7: U3.48 (RD7), U6.17 (DQ3), U8.17 (DQ3)
/VDP_CSR_N: R6.2, R11.1, U3.31 (~CSR)
/VDP_CSW_N: R5.2, R10.1, U3.30 (~CSW)
/VDP_D0: U1.18 (B0), U3.40 (CD0)
/VDP_D1: U1.17 (B1), U3.39 (CD1)
/VDP_D2: U1.16 (B2), U3.38 (CD2)
/VDP_D3: U1.15 (B3), U3.37 (CD3)
/VDP_D4: U1.14 (B4), U3.36 (CD4)
/VDP_D5: U1.13 (B5), U3.35 (CD5)
/VDP_D6: U1.12 (B6), U3.34 (CD6)
/VDP_D7: U1.11 (B7), U3.32 (CD7)
/VDP_MODE0: R3.2, R8.1, U3.29 (MODE0)
/VDP_MODE1: R4.2, R9.1, U3.28 (MODE1)
/VDP_PIN21: R43.2, SW2.2 (COM-A), U3.21 (VDD_DAC/VIDEO)
/VDP_RESET_N: R7.2, R12.1, U3.9 (~RESET)
/VRESET: RN1.10, U3.4 (~VRESET/~VDS)
/VWR: R21.2, U5.4 (~WE), U6.4 (~WE), U7.4 (~WE), U8.4 (~WE)
/VWR_RAW: R21.1, U3.57 (R/~W)
/WAIT_5: R18.2, U4.8 (1A4)
/WAIT_RAW: R18.1, R47.2, U3.26 (~WAIT/~LPS)
/XTAL1: C1.1, R2.1, U3.63 (XTAL1), Y1.1
/XTAL2: C2.1, R2.2, U3.64 (XTAL2), Y1.2

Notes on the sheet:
V9938/V9958 Pico Tester Revision B - B1.1 PROTOTYPE
All carrier-board parts are through-hole.
Power off before inserting or removing socketed ICs.
Prototype/unvalidated: verify mechanical fit and electrical levels before relying on results.
